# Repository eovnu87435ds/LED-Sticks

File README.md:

# LED-Sticks
some small, 4S capable LED sticks

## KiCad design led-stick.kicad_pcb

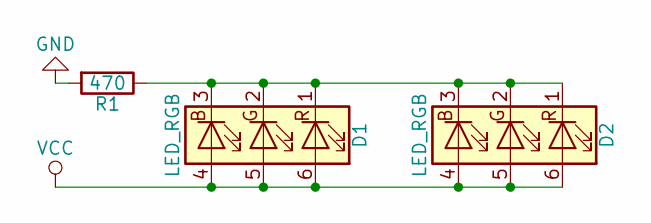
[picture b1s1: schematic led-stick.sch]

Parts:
D1, D2: LED_RGB; LED_RGB_PLCC-6
R1: 470; R_2010

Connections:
GND: R1.2
unnamed: D1.1 (RK), D1.2 (GK), D1.3 (BK), D2.1 (RK), D2.2 (GK), D2.3 (BK), R1.1
VCC: D1.4 (BA), D1.5 (GA), D1.6 (RA), D2.4 (BA), D2.5 (GA), D2.6 (RA)

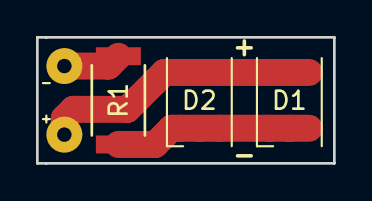
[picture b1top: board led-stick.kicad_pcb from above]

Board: 2 copper layers, 16.5 x 7.0 mm, 3 parts (0 on the bottom side), 2 nets.

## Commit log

2017-02-09 initial design of board
2017-02-09 added possible parts list
2017-02-09 ready for first fab
2017-02-09 changed silk placement
